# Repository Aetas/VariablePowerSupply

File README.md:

# VariablePowerSupply
~1.7V-29.9V/1.5A Variable power supply.

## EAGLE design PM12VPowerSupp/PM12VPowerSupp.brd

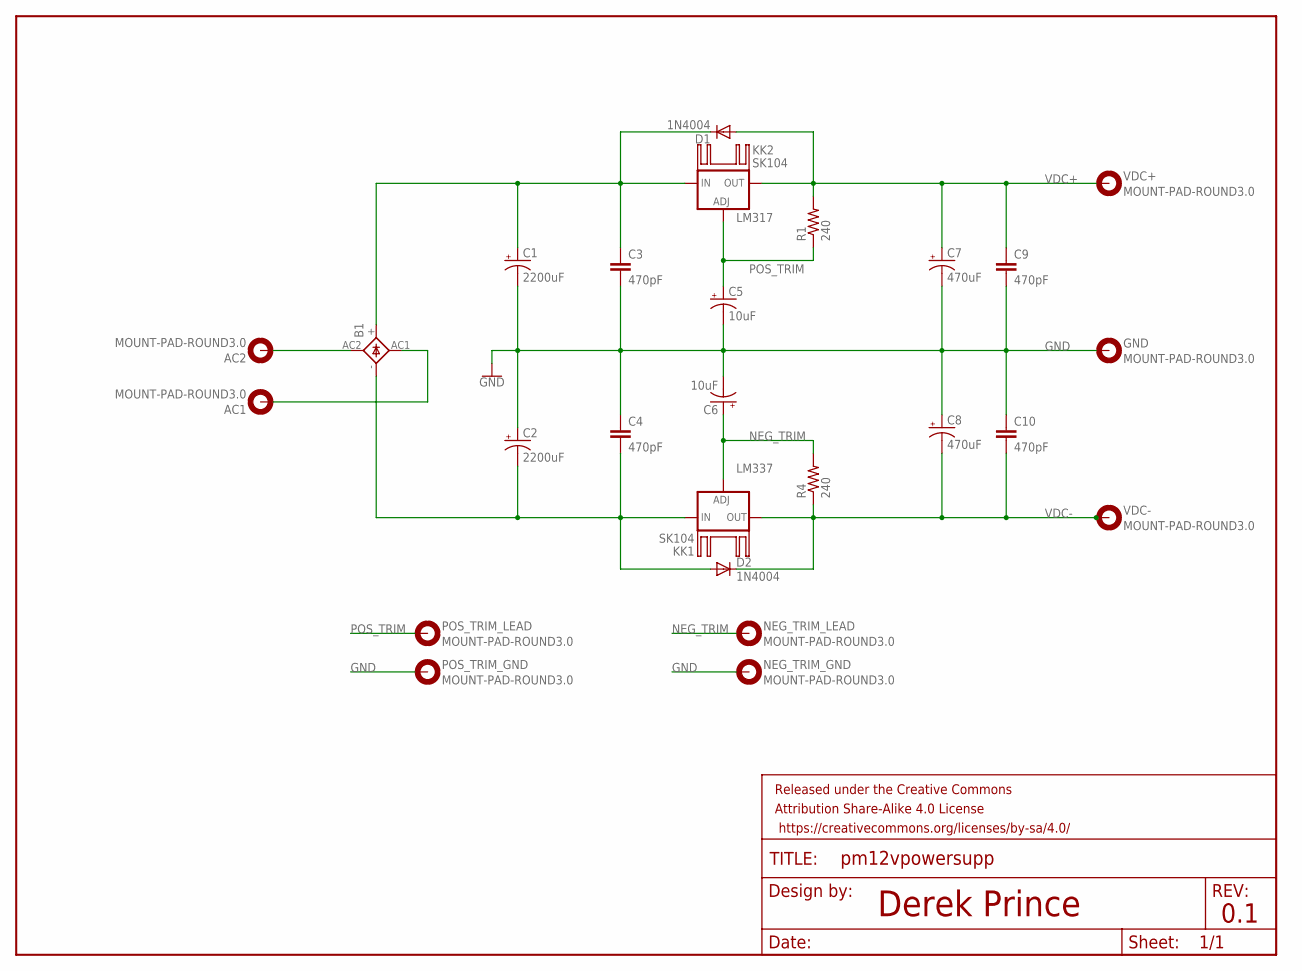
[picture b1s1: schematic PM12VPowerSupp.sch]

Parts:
AC1, AC2: MOUNT-PAD-ROUND3.0; 3,0-PAD
B1: GBU4; GBU4S
C1, C2: 2200uF; E7,5-16
C3, C4, C9, C10: 470pF; C050-024X044
C5, C6: 10uF; E2-5
C7, C8: 470uF; E5-10,5
D1, D2: 1N4004; DO41-10
FRAME1: FRAME-LETTER; CREATIVE_COMMONS
GND: MOUNT-PAD-ROUND3.0; 3,0-PAD
KK1, KK2: SK104
LM317: LM317TS; 317TS
LM337: LM337TS; 337TS
NEG_TRIM_GND: MOUNT-PAD-ROUND3.0; 3,0-PAD
NEG_TRIM_LEAD: MOUNT-PAD-ROUND3.0; 3,0-PAD
POS_TRIM_GND: MOUNT-PAD-ROUND3.0; 3,0-PAD
POS_TRIM_LEAD: MOUNT-PAD-ROUND3.0; 3,0-PAD
R1, R4: 240; 0309/12
VDC+: MOUNT-PAD-ROUND3.0; 3,0-PAD
VDC-: MOUNT-PAD-ROUND3.0; 3,0-PAD

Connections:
AC1_INPUT: AC1.B3,0, B1.AC1 (AC2)
GND: C1.-, C2.+, C3.2, C4.1, C5.-, C6.-, C7.-, C8.+, C9.2, C10.1, GND.B3,0, NEG_TRIM_GND.B3,0, POS_TRIM_GND.B3,0
unnamed: AC2.B3,0, B1.AC2 (AC1)
unnamed: B1.-, C2.-, C4.2, D2.A, LM337.2 (IN)
unnamed: B1.+, C1.+, C3.1, D1.C, LM317.3 (IN)
NEG_TRIM: C6.+, LM337.1 (ADJ), NEG_TRIM_LEAD.B3,0, R4.2
POS_TRIM: C5.+, LM317.1 (ADJ), POS_TRIM_LEAD.B3,0, R1.1
VDC+: C7.+, C9.1, D1.A, LM317.2 (OUT), R1.2, VDC+.B3,0
VDC-: C8.-, C10.2, D2.C, LM337.3 (OUT), R4.1, VDC-.B3,0

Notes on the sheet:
Derek Prince
0.1

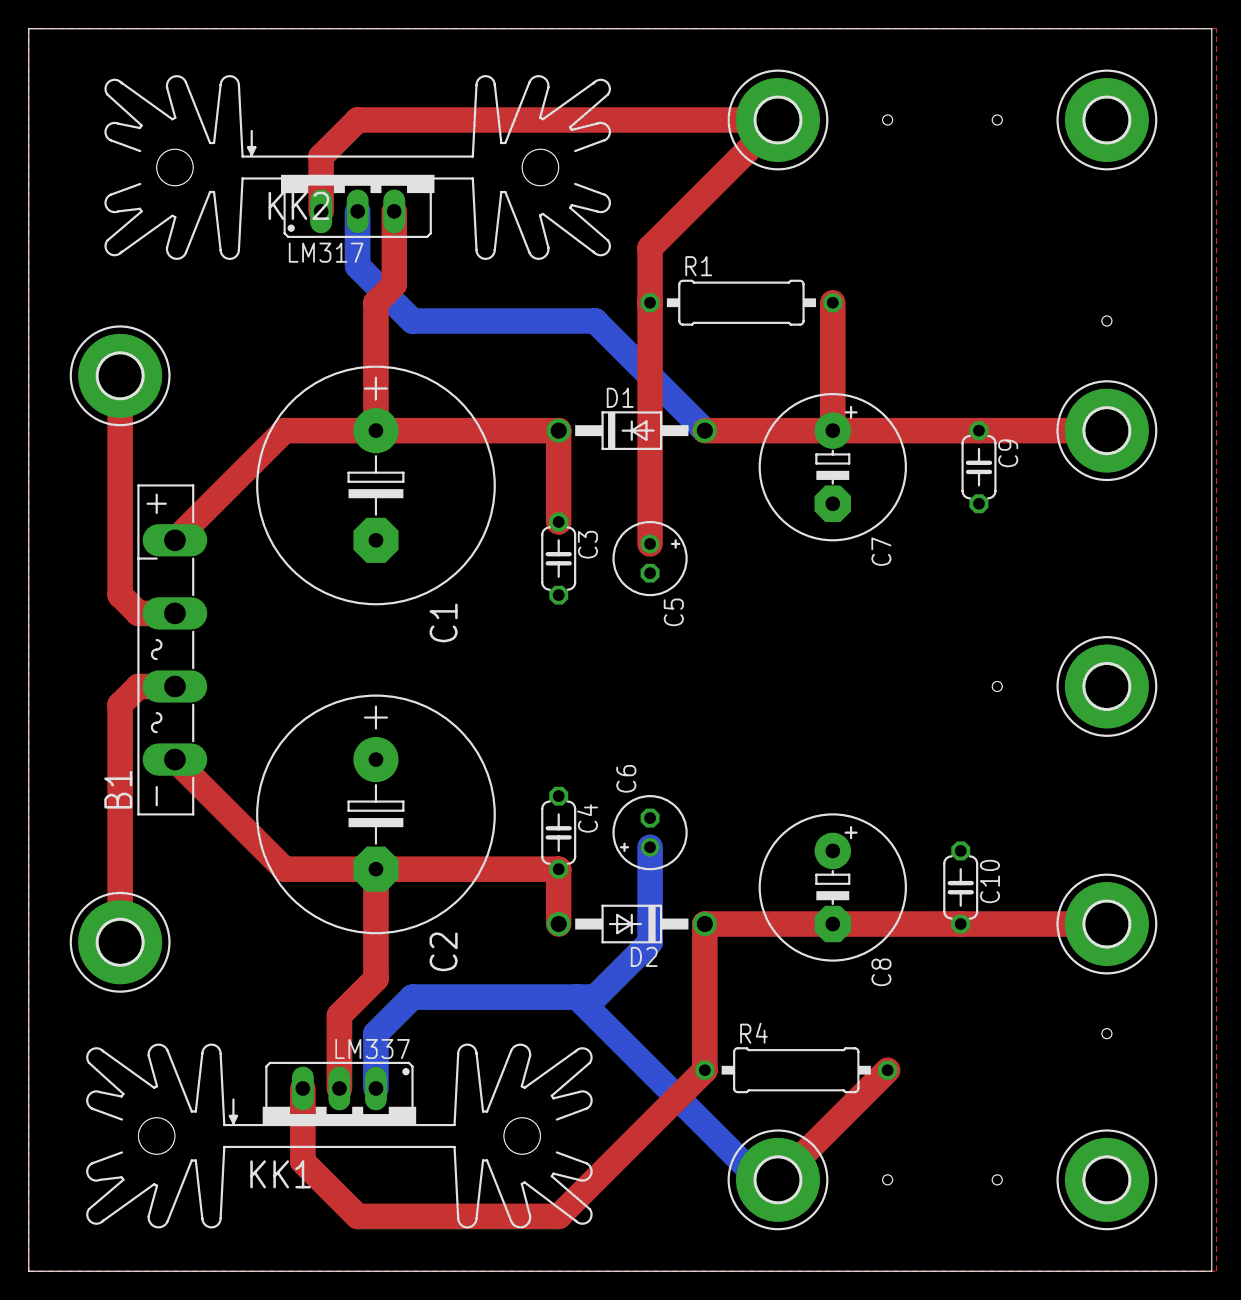
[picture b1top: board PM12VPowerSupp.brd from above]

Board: 2 copper layers, 82.2 x 86.3 mm, 29 parts (0 on the bottom side), 9 nets.

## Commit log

2016-12-23 Eagle file
2016-12-23 schematic largely done, need to do board
2016-12-24 Started board design. Heat sink sink-pins need some thought for the last traces. Also, beer.
2016-12-25 No more air wires. Have to do relief holes and heat sinks
2017-01-07 Initial LTSpice schematic. No values. Regulators untested.
2017-01-07 Revert "No more air wires. Have to do relief holes and heat sinks"
    This reverts commit 0472ab177aecc554d98bdcb29c09631f317f4fda.
2017-01-08 Added cap values and the diodes briding I/O on regs
2017-01-16 I don't know why I added this since it wont work on any machine that downloads it.
2017-01-16 Added a ghetto negative workaround. It works though.
2017-01-16 Added todo file.
2017-01-19 Added ground bit before I fortgot again.

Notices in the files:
parts and their libraries:
SparkFun-Aesthetics: Licensing: Creative Commons ShareAlike 4.0 International - https://creativecommons.org/licenses/by-sa/4.0
SparkFun-Aesthetics: Released under the Creative Commons Attribution Share-Alike 4.0 License
SparkFun-Aesthetics: https://creativecommons.org/licenses/by-sa/4.0
